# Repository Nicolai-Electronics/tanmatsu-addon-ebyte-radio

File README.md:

# Tanmatsu add-on: Ebyte radio modules

This repository contains the hardware design files for the Ebyte radio modules addon for the internal add-on connector of Tanmatsu.

## Documentation

Need the schematic? [It's in this repository as a PDF file](schematic.pdf).

## License

This hardware design may be used under the terms of the [CERN-OHL-P](LICENSE) license.

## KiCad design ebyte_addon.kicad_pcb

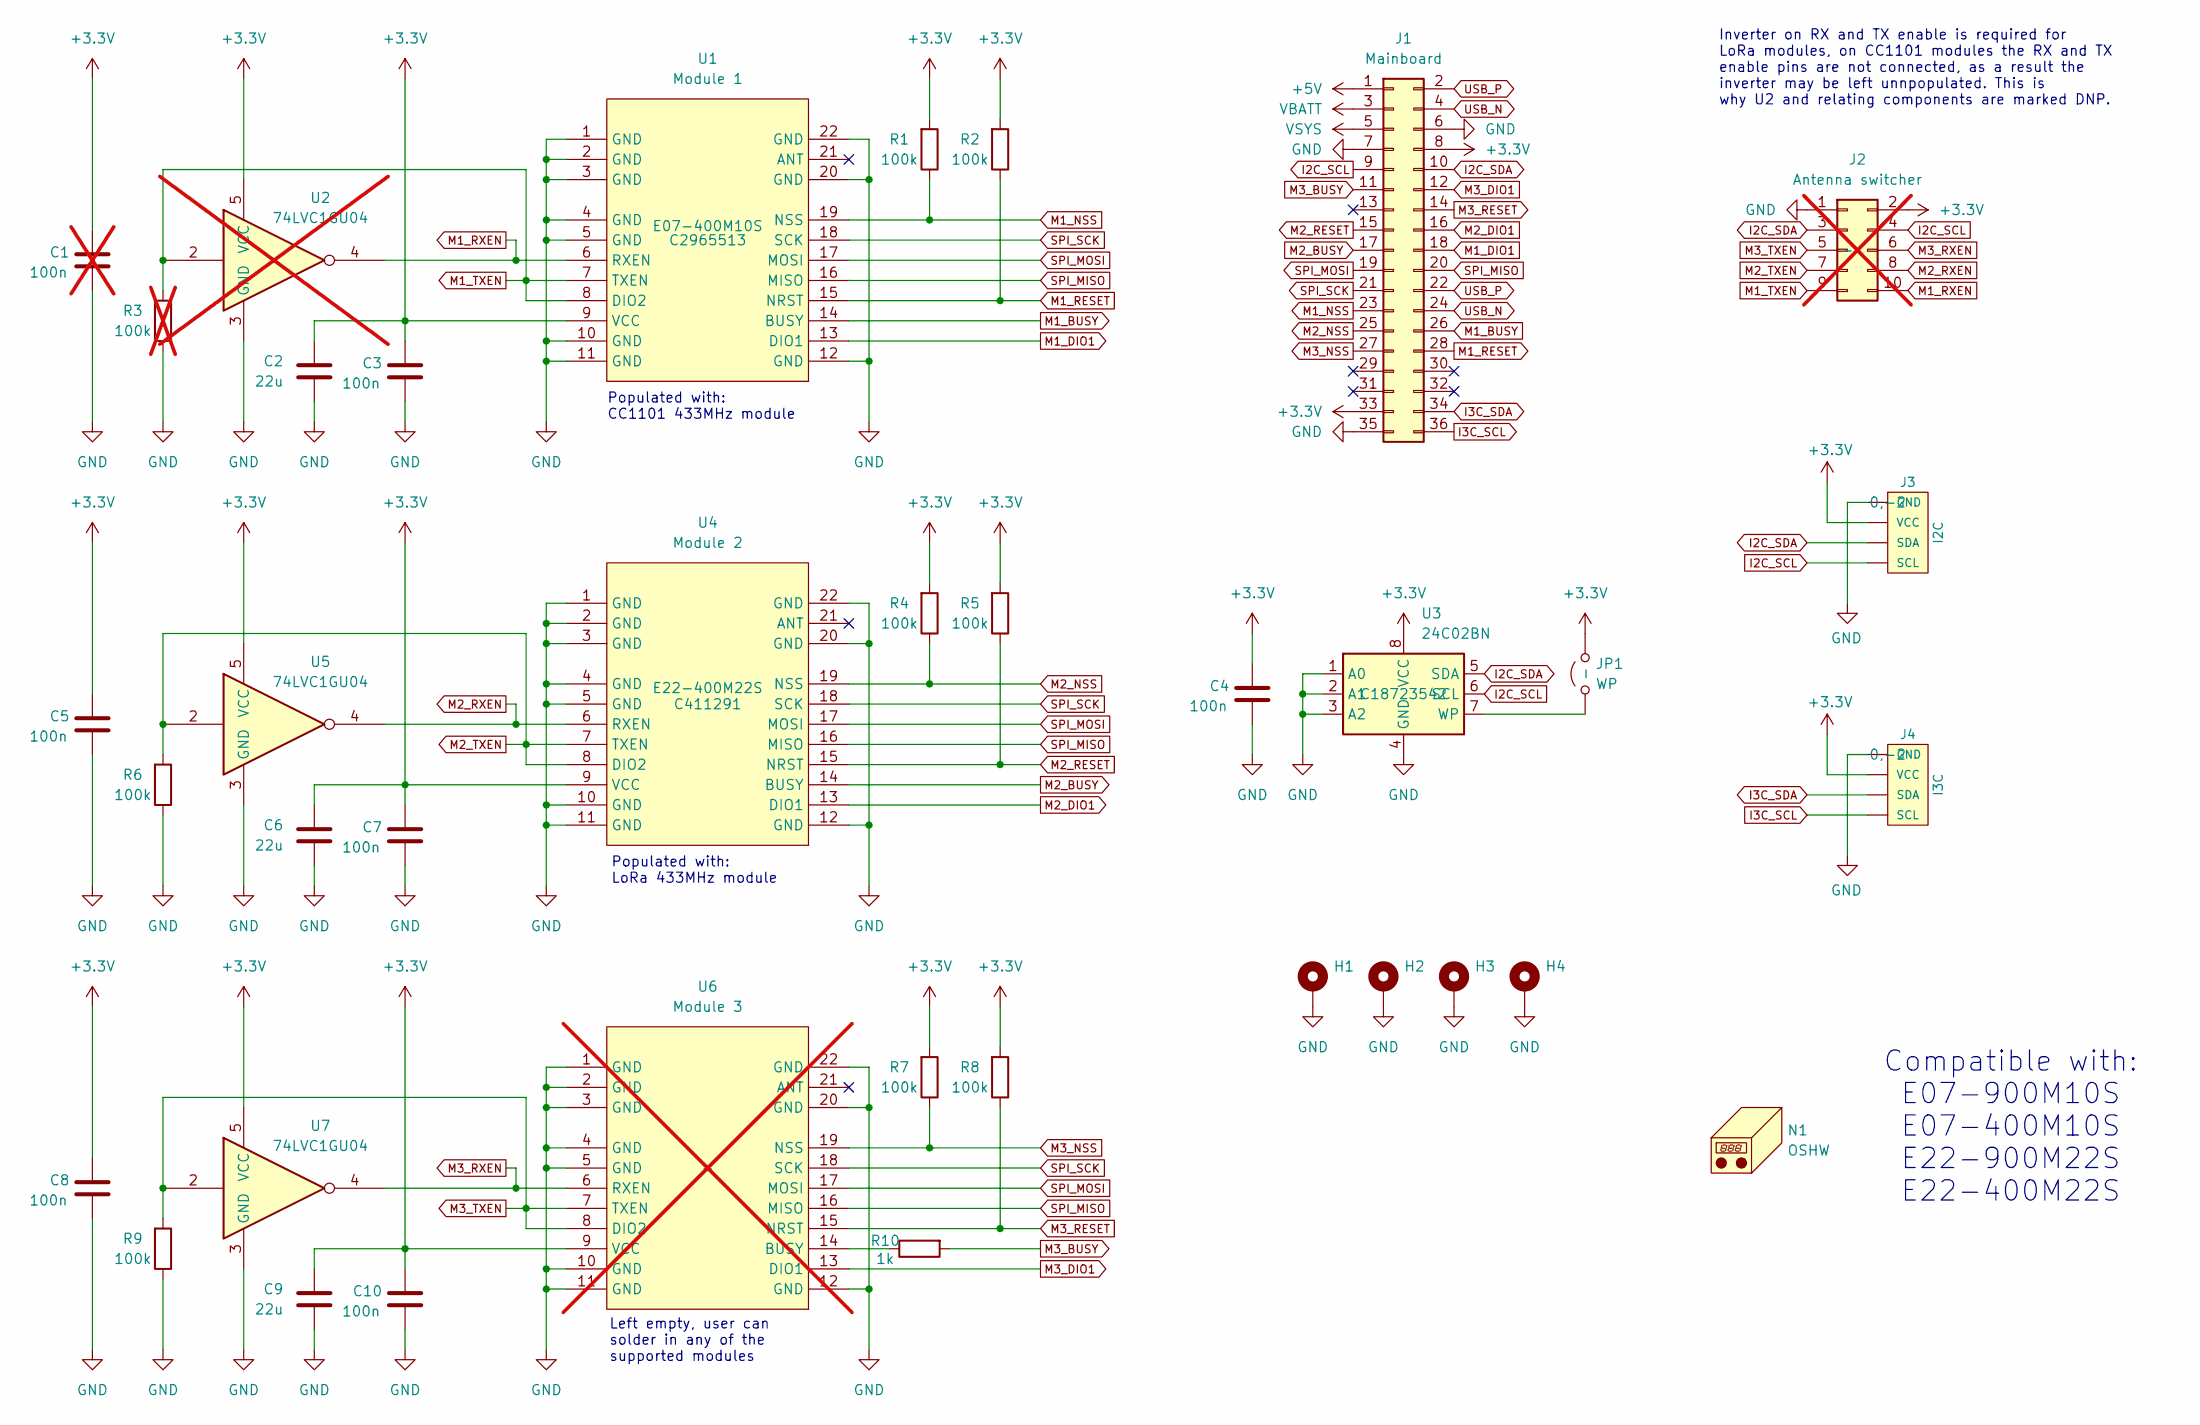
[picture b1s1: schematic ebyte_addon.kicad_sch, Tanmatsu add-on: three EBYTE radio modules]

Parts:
C1: 100n; C_0402_1005Metric; LCSC C307331; not fitted
C2, C6, C9: 22u; C_0805_2012Metric; LCSC C602037
C3, C4, C5, C7, C8, C10: 100n; C_0402_1005Metric; LCSC C307331
H1, H2, H3, H4: MountingHole_2.2mm_M2_Pad_Via
J1: Mainboard; PinHeader_2x18_P2.54mm_Vertical_SMD; LCSC C6332243
J2: Antenna switcher; PinHeader_2x05_P2.54mm_Vertical; not fitted
J3: I2C; 1X04_1MM_RA_GND; LCSC C7433425
J4: I3C; 1X04_1MM_RA_GND; LCSC C7433425
JP1: WP; SolderJumper-2_P1.3mm_Open_TrianglePad1.0x1.5mm
N1: OSHW; OSHW-Logo2_9.8x8mm_SilkScreen
R1, R2, R4, R5, R6, R7, R8, R9: 100k; R_0402_1005Metric; LCSC C25741
R3: 100k; R_0402_1005Metric; LCSC C25741; not fitted
R10: 1k; R_0402_1005Metric; LCSC C11702
U1: Module 1; WIRELM-SMD_E22-900M22S; LCSC C2965513
U2: 74LVC1GU04; SOT-353_SC-70-5; LCSC C485082; not fitted
U3: 24C02BN; SOP-8_3.9x4.9mm_P1.27mm; LCSC C18723542
U4: Module 2; WIRELM-SMD_E22-900M22S; LCSC C411291
U5, U7: 74LVC1GU04; SOT-353_SC-70-5; LCSC C485082
U6: Module 3; WIRELM-SMD_E22-900M22S; not fitted

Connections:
+3.3V: C1.1, C2.1, C3.1, C4.1, C5.1, C6.1, C7.1, C8.1, C9.1, C10.1, J1.8, J1.33, J2.2, J3.2 (VCC), J4.2 (VCC), JP1.2 (B), R1.2, R2.2, R4.2, R5.2, R7.2, R8.2, U1.9 (VCC), U2.5 (VCC), U3.8 (VCC), U4.9 (VCC), U5.5 (VCC), U6.9 (VCC), U7.5 (VCC)
+5V: J1.1
GND: C1.2, C2.2, C3.2, C4.2, C5.2, C6.2, C7.2, C8.2, C9.2, C10.2, H1.1, H2.1, H3.1, H4.1, J1.6, J1.7, J1.35, J2.1, J3.1 (GND), J3.5, J3.6, J4.1 (GND), J4.5, J4.6, R3.1, R6.1, R9.1, U1.1 (GND), U1.2 (GND), U1.3 (GND), U1.4 (GND), U1.5 (GND), U1.10 (GND), U1.11 (GND), U1.12 (GND), U1.20 (GND), U1.22 (GND), U2.3 (GND), U3.1 (A0), U3.2 (A1), U3.3 (A2), U3.4 (GND), U4.1 (GND), U4.2 (GND), U4.3 (GND), U4.4 (GND), U4.5 (GND), U4.10 (GND), U4.11 (GND), U4.12 (GND), U4.20 (GND), U4.22 (GND), U5.3 (GND), U6.1 (GND), U6.2 (GND), U6.3 (GND), U6.4 (GND), U6.5 (GND), U6.10 (GND), U6.11 (GND), U6.12 (GND), U6.20 (GND), U6.22 (GND), U7.3 (GND)
I2C_SCL: J1.9, J2.4, J3.4 (SCL), U3.6 (SCL)
I2C_SDA: J1.10, J2.3, J3.3 (SDA), U3.5 (SDA)
I3C_SCL: J1.36, J4.4 (SCL)
I3C_SDA: J1.34, J4.3 (SDA)
M1_BUSY: J1.26, U1.14 (BUSY)
M1_DIO1: J1.18, U1.13 (DIO1)
M1_NSS: J1.23, R1.1, U1.19 (NSS)
M1_RESET: J1.28, R2.1, U1.15 (NRST)
M1_RXEN: J2.10, U1.6 (RXEN), U2.4
M1_TXEN: J2.9, R3.2, U1.7 (TXEN), U1.8 (DIO2), U2.2
M2_BUSY: J1.17, U4.14 (BUSY)
M2_DIO1: J1.16, U4.13 (DIO1)
M2_NSS: J1.25, R4.1, U4.19 (NSS)
M2_RESET: J1.15, R5.1, U4.15 (NRST)
M2_RXEN: J2.8, U4.6 (RXEN), U5.4
M2_TXEN: J2.7, R6.2, U4.7 (TXEN), U4.8 (DIO2), U5.2
M3_BUSY: J1.11, R10.2
M3_DIO1: J1.12, U6.13 (DIO1)
M3_NSS: J1.27, R7.1, U6.19 (NSS)
M3_RESET: J1.14, R8.1, U6.15 (NRST)
M3_RXEN: J2.6, U6.6 (RXEN), U7.4
M3_TXEN: J2.5, R9.2, U6.7 (TXEN), U6.8 (DIO2), U7.2
unnamed: JP1.1 (A), U3.7 (WP)
unnamed: R10.1, U6.14 (BUSY)
SPI_MISO: J1.20, U1.16 (MISO), U4.16 (MISO), U6.16 (MISO)
SPI_MOSI: J1.19, U1.17 (MOSI), U4.17 (MOSI), U6.17 (MOSI)
SPI_SCK: J1.21, U1.18 (SCK), U4.18 (SCK), U6.18 (SCK)
USB_N: J1.4, J1.24
USB_P: J1.2, J1.22
VBATT: J1.3
VSYS: J1.5

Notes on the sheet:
Inverter on RX and TX enable is required for LoRa modules, on CC1101 modules the RX and TX enable pins are not connected, as a result the inverter may be left unnpopulated. This is why U2 and relating components are marked DNP.
Compatible with: E07-900M10S E07-400M10S E22-900M22S E22-400M22S
Left empty, user can solder in any of the supported modules
Populated with: LoRa 433MHz module
Populated with: CC1101 433MHz module

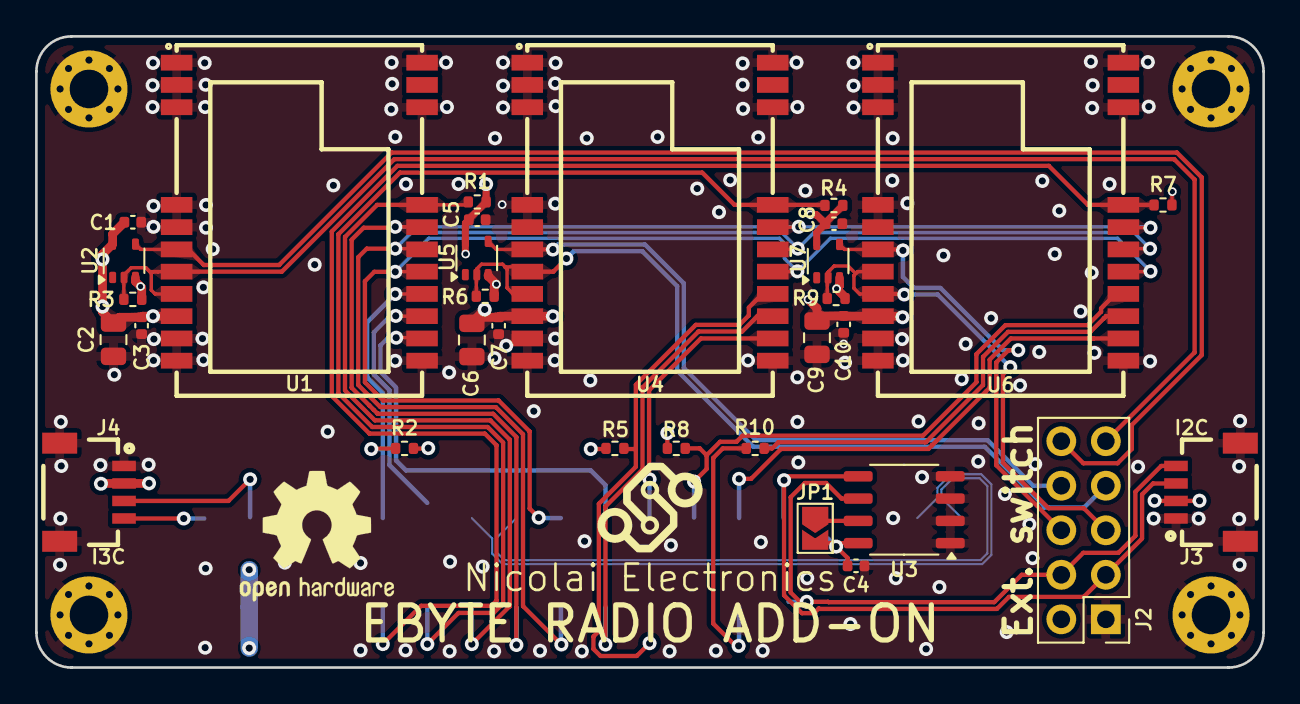
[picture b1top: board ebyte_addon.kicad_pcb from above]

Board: 4 copper layers, 70.0 x 36.0 mm, 37 parts (1 on the bottom side), 31 nets.

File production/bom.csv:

Designator,Footprint,Quantity,Value,LCSC Part #
"C10, C3, C4, C5, C7, C8",0402,6,100n,C307331
"C2, C6, C9",0805,3,22u,C602037
J1,PinHeader_2x18_P2.54mm_Vertical_SMD,1,Mainboard,C6332243
J2,PinHeader_2x05_P2.54mm_Vertical,1,Antenna switcher,-
J3,1X04_1MM_RA_GND,1,I2C,C7433425
J4,1X04_1MM_RA_GND,1,I3C,C7433425
"R1, R2, R4, R5, R6, R7, R8, R9",0402,8,100k,C25741
R10,0402,1,1k,C11702
U1,WIRELM-SMD_E22-900M22S,1,Module 1,C2965513
U3,SOP-8_3.9x4.9mm_P1.27mm,1,24C02BN,C18723542
U4,WIRELM-SMD_E22-900M22S,1,Module 2,C411291
"U5, U7",SOT-353_SC-70-5,2,74LVC1GU04,C485082
U6,WIRELM-SMD_E22-900M22S,1,Module 3,-

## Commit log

2025-05-16 Fix connector orientation
2025-05-16 Configure first two radio modules to be populated by manufacturer
2025-05-17 Rename files, add schematic and add notes to schematic
2025-05-20 Add missing LICENSE file

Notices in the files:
ebyte_addon.kicad_sch:
License: CERN-OHL-P
Copyright © 2025 Nicolai Electronics
